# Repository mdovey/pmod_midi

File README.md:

# pmod_midi
#### PMOD Adapter for the CME Widi Core BLE MIDI module

Kicad files for a PCB adapter board/shield to allow the [CME Widi Core module](https://www.cme-pro.com/widi-core/) to be connected to development boards which use the [Digilent PMOD connector](https://digilent.com/shop/about-system-boards-and-components/).

| PMOD Pin | Core Pin | Notes                                                        |
| -------- | -------- | ------------------------------------------------------------ |
| 1        | 1 (TX)   | Connects directly to Widi Core TX pin for MIDI over UART     |
| 2        | 11 (RX)  | Connects directly to Widi Core RX pin for MIDI over UART     |
| 3        | 6 (ON)   | Connects to Widi Core ON pin via pull down resistor. Active high to enable the Widi Core module. |
| 4        | 12 (RS)  | Connects to Widi Core RS pin. Active low reset.              |
| 7        | 16 (S1)  | Connects to Widi Core S1 pin. Bluetooth connection status (0 = Not connected, 1 = Connected). |
| 8        | 15 (S2)  | Connects to Widi Core C2 pin. Bluetooth role (0 = peripheral, 1 = central) |
| 9        | 13 (SF)  | Connects to Widi Core SF pin. Baud rate (0 = 31.25 Kb/s, 1 = 100 Kb/s). Requires reset cycle to execute change. |
| 10       | 14 (BT)  | If 1, shorts Widi Core BT pin to ground - simulating button press. |

The board also has a push button which shorts Widi Core pin 14 (BT) to ground (for factory reset and bluetooth role change), and an RGB LED, powered by Widi Core pins 2 (LB), 3(LG), 4 (LR) and 5(V3), for status information (see [CME Widi Core datasheet](https://www.cme-pro.com/wp-content/uploads/2022/10/widiCore-Doc-v1.3.pdf), page 9). An optional 0.5 inch pitch header can provide access to the Widi Core pins 9 (TMS) and 10 (TCK)

The [BOM](./kicad/pmod_midi_bom.md) includes sockets to allow the CME Widi Core (or the Core N/XN with suitable headers) to be inserted and removed. Alternatively the Core N/XN can be hard soldered for example using 0.1 inch pitch header pins.

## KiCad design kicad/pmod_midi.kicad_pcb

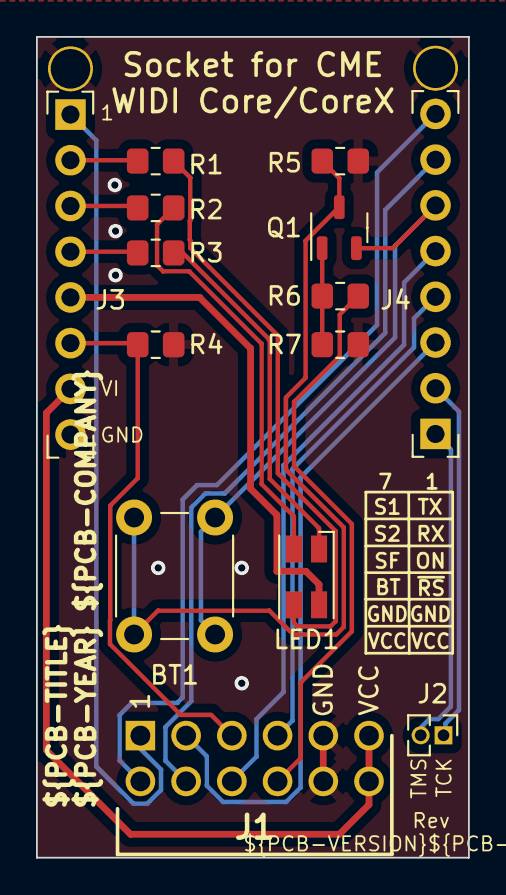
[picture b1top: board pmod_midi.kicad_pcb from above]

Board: 2 copper layers, 24.0 x 45.6 mm, 16 parts (0 on the bottom side), 22 nets.

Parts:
BT1: SW_Push; SW_PUSH_6mm
H1, H2: MountingHole_Pad; Standoff Spacer
J1: PMOD (12 Pin)
J2: Conn_01x02_Pin; PinHeader_1x02_P1.27mm_Vertical
J3: CME_Widi_Core_1-8; CME Widi Core Socket Pins 1 - 8
J4: CME_Widi_Core_9-16; CME Widi Core Socket Pins 9 - 16
LED1: LED_ABRG; LED_RGB_Wuerth-PLCC4_3.2x2.8mm_150141M173100
Q1: Q_NPN_BCE; SOT-23-3
R1, R2, R5: 680; R_0805_2012Metric_Pad1.20x1.40mm_HandSolder
R3: 820; R_0805_2012Metric_Pad1.20x1.40mm_HandSolder
R4, R6: 1k; R_0805_2012Metric_Pad1.20x1.40mm_HandSolder
R7: 10k; R_0805_2012Metric_Pad1.20x1.40mm_HandSolder

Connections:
/3.3V: J1.6 (VCC), J1.12 (VCC), J3.7 (VI)
/BLUE: LED1.2 (BK), R1.1
/BT: J1.10, R6.2
/BT*: Q1.1 (B), R6.1, R7.1
/GND: H1.1, H2.1, J1.5 (GND), J1.11 (GND), J3.8 (GND), R4.1, R5.1, R7.2
/GND*: BT1.2, Q1.3 (E), R5.2
/GREEN: LED1.4 (GK), R2.1
/LB: J3.2 (LB), R1.2
/LG: J3.3 (LG), R2.2
/LR: J3.4 (LR), R3.2
/ON: J1.3, J3.6 (ON), R4.2
/RED: LED1.3 (RK), R3.1
/RX: J1.2, J4.11 (RX)
/S1: J1.7, J4.16 (S1)
/S2: J1.8, J4.15 (S2)
/SF: J1.9, J4.13 (SF)
/TCK: J2.1 (TCK), J4.10 (TCK)
/TMS: J2.2 (TMS), J4.9 (TMS)
/TX: J1.1, J3.1 (TX)
/V3: J3.5 (V3), LED1.1 (A)
/~BT: BT1.1, J4.14 (~BT), Q1.2 (C)
/~RS: J1.4, J4.12 (~RS)

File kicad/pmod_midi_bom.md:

# pmod_midi.kicad_sch BOM

05/08/2023 12:28:57

Generated from schematic by Eeschema 7.0.6

**Component Count:** 20

| Refs | Qty | Component | Description | Manufacturer | MPN | Notes |
| ----- | --- | ---- | ----------- | ---- | ---- | ---- |
| BT1 | 1 | SW_Push | Push button switch, generic, two pins | CUI | [TS02-66-60-BK-160-LCR-D](https://www.mouser.co.uk/datasheet/2/670/ts02-2586188.pdf) | 6mm momentarily closed tactile button switch |
| H1, H2 | 2 | MountingHole_Pad | Mounting Hole with connection | Würth Elektronik | [970100244](https://www.we-online.com/components/products/datasheet/9701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 | Optional: 10mm M2 female to female standoff spacer,  |
| J1 | 1 | PMOD (12 Pin) | Digilent 12 Pin PMOD Connector | Samtec | [TSW-106-08-L-D-RA](https://suddendocs.samtec.com/catalog_english/tsw_th.pdf) | 2x6 0.1 Inch pitch right-angle pin header |
| J2 | 1 | Conn_01x02_Pin | Generic connector, single row, 01x02, script generated | Mill-Max | [852-10-002-10-001000](https://www.mill-max.com/catalog/download/2017-11:034.pdf) | Optional: 1x2 0.05 Inch pitch pin header |
| J3 | 1 | CME_Widi_Core_1-8 | CME Widi Core - Pins 1 - 8 | Samtec | [SSW-108-01-L-S](https://suddendocs.samtec.com/catalog_english/ssw_th.pdf) | 1x8 0.1 Inch pitch pin header socket; . For insertion of pins 1-8 of [CME Widi Core module](https://www.cme-pro.com/wp-content/uploads/2022/10/widiCore-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 |
| J4 | 1 | CME_Widi_Core_9-16 | CME Widi Core - Pins 9 - 16 | Samtec | [SSW-108-01-L-S](https://suddendocs.samtec.com/catalog_english/ssw_th.pdf) | 1x8 0.1 Inch pitch pin header socket; . For insertion of pins 9-16 of [CME Widi Core module](https://www.cme-pro.com/wp-content/uploads/2022/10/widiCore-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 |
| LED1 | 1 | LED_ABRG | RGB LED, anode/blue/red/green | Würth Elektronik | [150141M173100](https://www.we-online.com/components/products/datasheet/1501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 | 3528 SMD Common Anode RGB LED (Parity Pin 1 - Red Cathode) |
| Q1 | 1 | Q_NPN_BCE | NPN transistor, base/collector/emitter | STMicroelectronics | [2STR2160](https://www.st.com/resource/en/datasheet/2str2160.pdf) | SOT-23 3 SMD NPN Transistor (Pin order: BCE) |
| R1, R2, R5 | 3 | 680 | Resistor |  | 680 ohm 0805 SMD Resistor |  |
| R3 | 1 | 820 | Resistor |  | 820 ohm 0805 SMD Resistor |  |
| R4, R6 | 2 | 1k | Resistor |  | 1k ohm 0805 SMD Resistor |  |
| R7 | 1 | 10k | Resistor |  | 10k ohm 0805 SMD Resistor |  |
| U1–4 | 4 | M2 Nylon Machine Screw | Machine Screw | Essentra | [50M020040D004](https://www.essentracomponents.com/en-us/p/nylon-cheese-head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 | Optional: M2 4mm nylon pan head machine screw |

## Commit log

2023-07-26 Initial PCB layout
2023-07-26 added photo
2023-07-26 Tidied footprints
2023-07-27 Added BOM
2023-07-27 Tidying
2023-08-01 Updated BOM

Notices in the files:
README.md:
License: GPL v3
